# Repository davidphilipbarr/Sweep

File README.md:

# Sweep
<!--
           ___                        ___
      ___ |   | ___ ___      ___ ___ |   | ___
 ___ |   |`___`|   |   |    |   |   |`___`|   | ___
|   |`___`|   |`___`___`    `___`___`|   |`___`|   |
`___`|   |`___`|   |   |    |   |   |`___`|   |`___`
|   |`___`|   |`___`___`    `___`___`|   |`___`|   |
`___`|   |`___`|   |   |    |   |   |`___`|   |`___`
|   |`___`     `___`___`    `___`___`     `___`|   |
`___`           ___ ___      ___ ___           `___`
               |   |   |    |   |   |
               `___`___`    `___`___`
-->
>    
> <sub>Bluetooth Sweep 2 + MBK Legend Keycaps</sub>

<span>

</span>

## What is sweep?

Sweep is a version of the more fabulous [Ferris](https://github.com/pierrechevalier83/ferris) by [Pierre Chevalier](https://github.com/pierrechevalier83/) that uses a daughter board like a promicro, elite-c, bit-c, nice!nano etc. instead of using onboard components.

## What are the different types?

⭐ Sweep 2 - Recommended Choc v1 board with all the features.  
⭕ Sweep Half Swept - Same as Sweep 2, but with a reversible pro-micro footprint.  
⭕ Sweep Bling MX - An MX only Sweep that features Kailh's hotswap sockets and a stacked case.  
⭕ Sweep Bling LP - A Choc v1 only Sweep that features Kailh's hotswap sockets.  
⭕ Sweep High - Same as the Sweep 2, but trades choc spacing for compatibility with more switches and keycaps.  
⭕ Sweep High M - A soldered MX only Sweep, with a reversible PCB design.  
⭕ Sweep Mini - The only version that supports Choc minis.  
⭕ Sweep ULP - A version for the Cherry Ultra low profile switches.  

| Device | On/Off Switch<sup>[1]</sup> | Reversible PCB<sup>[2]</sup> | Choc V1 | Choc V2 | Choc Mini | MX & Alps | Cherry ULP | Choc Spacing<sup>[3]</sup> | Tenting<sup>[4]</sup> | Hot Swap |
| :--- | :---: | :---: | :---: | :---: | :---: | :---: | :---: | :---: | :---: | :---: |
| Sweep2.x          | ✔ |   | ✔ |   |   |   |   | ✔ | ✔ | Mill-Max (optional) |
| Sweep Bling LP    | ✔ |   | ✔ |   |   |   |   | ✔ | ✔ | Kailh (required) |
| Sweep Bling MX    | ✔ | ✔ |   |   |   | ⚠<br/><sup>[5]</sup> |   |   | ✔ | Kailh (required) |
| Sweep High        | ✔ |   | ✔ | ✔ |   | ✔ |   |   | ✔ |
| Sweep High M      | ✔ | ✔ |   |   |   | MX|   |   | ✔ |   |
| Sweep Half Swept  | ✔ | ✔ | ✔ |   |   |   |   | ✔ | ✔ | Mill-Max (optional) |
| Sweep Mini        |   | ✔ |   |   | ✔ |   |   | ✔ |   |
| Sweep ULP         | ✔ |   |   |   |   |   | ✔ | ✔ |   |

> Note: All versions support bluetooth with Nice!Nano

*<sup>[1]</sup> An on/off switch is recommended for bluetooth builds.*  
*<sup>[2]</sup> With a reversible PCB it's easier to make mistakes during assembly, but it allows you to purchase less boards.*  
*<sup>[3]</sup> Choc spaced boards have the switches in a tighter grid. This provides a better final look but is only compatible with some choc keycaps. (e.g. MBK)*  
*<sup>[4]</sup> Supports splitkb's [tenting puck.](https://splitkb.com/products/tenting-puck?_pos=1&_psq=tenting%20&_ss=e&_v=1.0)*  
*<sup>[5]</sup> MX + kailh hotswap ONLY. Alps are NOT supported.*  

## Components list

To build and use a Sweep you will need:

* 1x PCB Kit
* 2x promicro compatible boards or 2 nice!nanos.
* 34 switches of a compatible type (refer to the compatibility table)
* 34 keycaps
* 2x reset switches (optional; [B3U-1000P(M)](https://github.com/davidphilipbarr/Sweep/issues/20))
* Some little rubber feet/bumpers
* 2x power switches (optional if supported; MSK 12C02)
* 1x TRRS (not TRS!) cable (wired build only)
* 2x TRRS Jack [PJ-320A] (wired build only)
* 1 USB Cable (depends on your micro-controller choice)

## How do I make this thing?

## Firmware

The firmware can be found [with the Ferris  firmware as part of QMK](https://github.com/qmk/qmk_firmware/tree/master/keyboards/ferris/sweep).

Firmware for zmk and bluemicro_ble is called ["Cradio"](https://zmk.dev/docs/hardware/).

## Who made this?

* [Pierre Chevalier](https://github.com/pierrechevalier83)
* [David Barr](https://github.com/davidphilipbarr)
* [Ibnu Daru Aji](https://github.com/ibnuda/)
* [Duccio](https://github.com/duckyb)

## Featured Forks ✨

* [Sweep Gateron](https://github.com/drewlwhitney/Sweep-Gateron) by drewlwhitney: *A Sweep High modded with Gateron-LP KS-33 support.*

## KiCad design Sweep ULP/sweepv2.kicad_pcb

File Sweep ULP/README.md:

# Sweep2

This is the ultra low profile version of the sweep.

## Ordering The PCB

To order the PCB the following settings are recommended<sup>1,2</sup>:

|Detail|Value|
|---|---|
|Gerber file|`production/sweepv2.zip`|
|Base material|FR-4|
|Layers|2|
|Dimension|216.9mm x 86.9mm|
|Different design|2|
|Delivery format|Panel by customer|
|PCB thickness|0.6mm|
|PCB color|(Personal preference)|
|Silkscreen|(Personal preference)|
|Surface finish|(Personal preference)|
|Outer copper weight|1oz|
|Gold Fingers|No|
|Confirm production file|No|
|Castellated holes|No|
|Remove order number|Yes|

1: Settings are for [JLCPCB](https://jlcpcb.com/), but could work for other manufacturers.

2: Settings are taken from [Kyek's video guide](https://www.youtube.com/watch?v=fBPu7AyDtkM&t=17s).

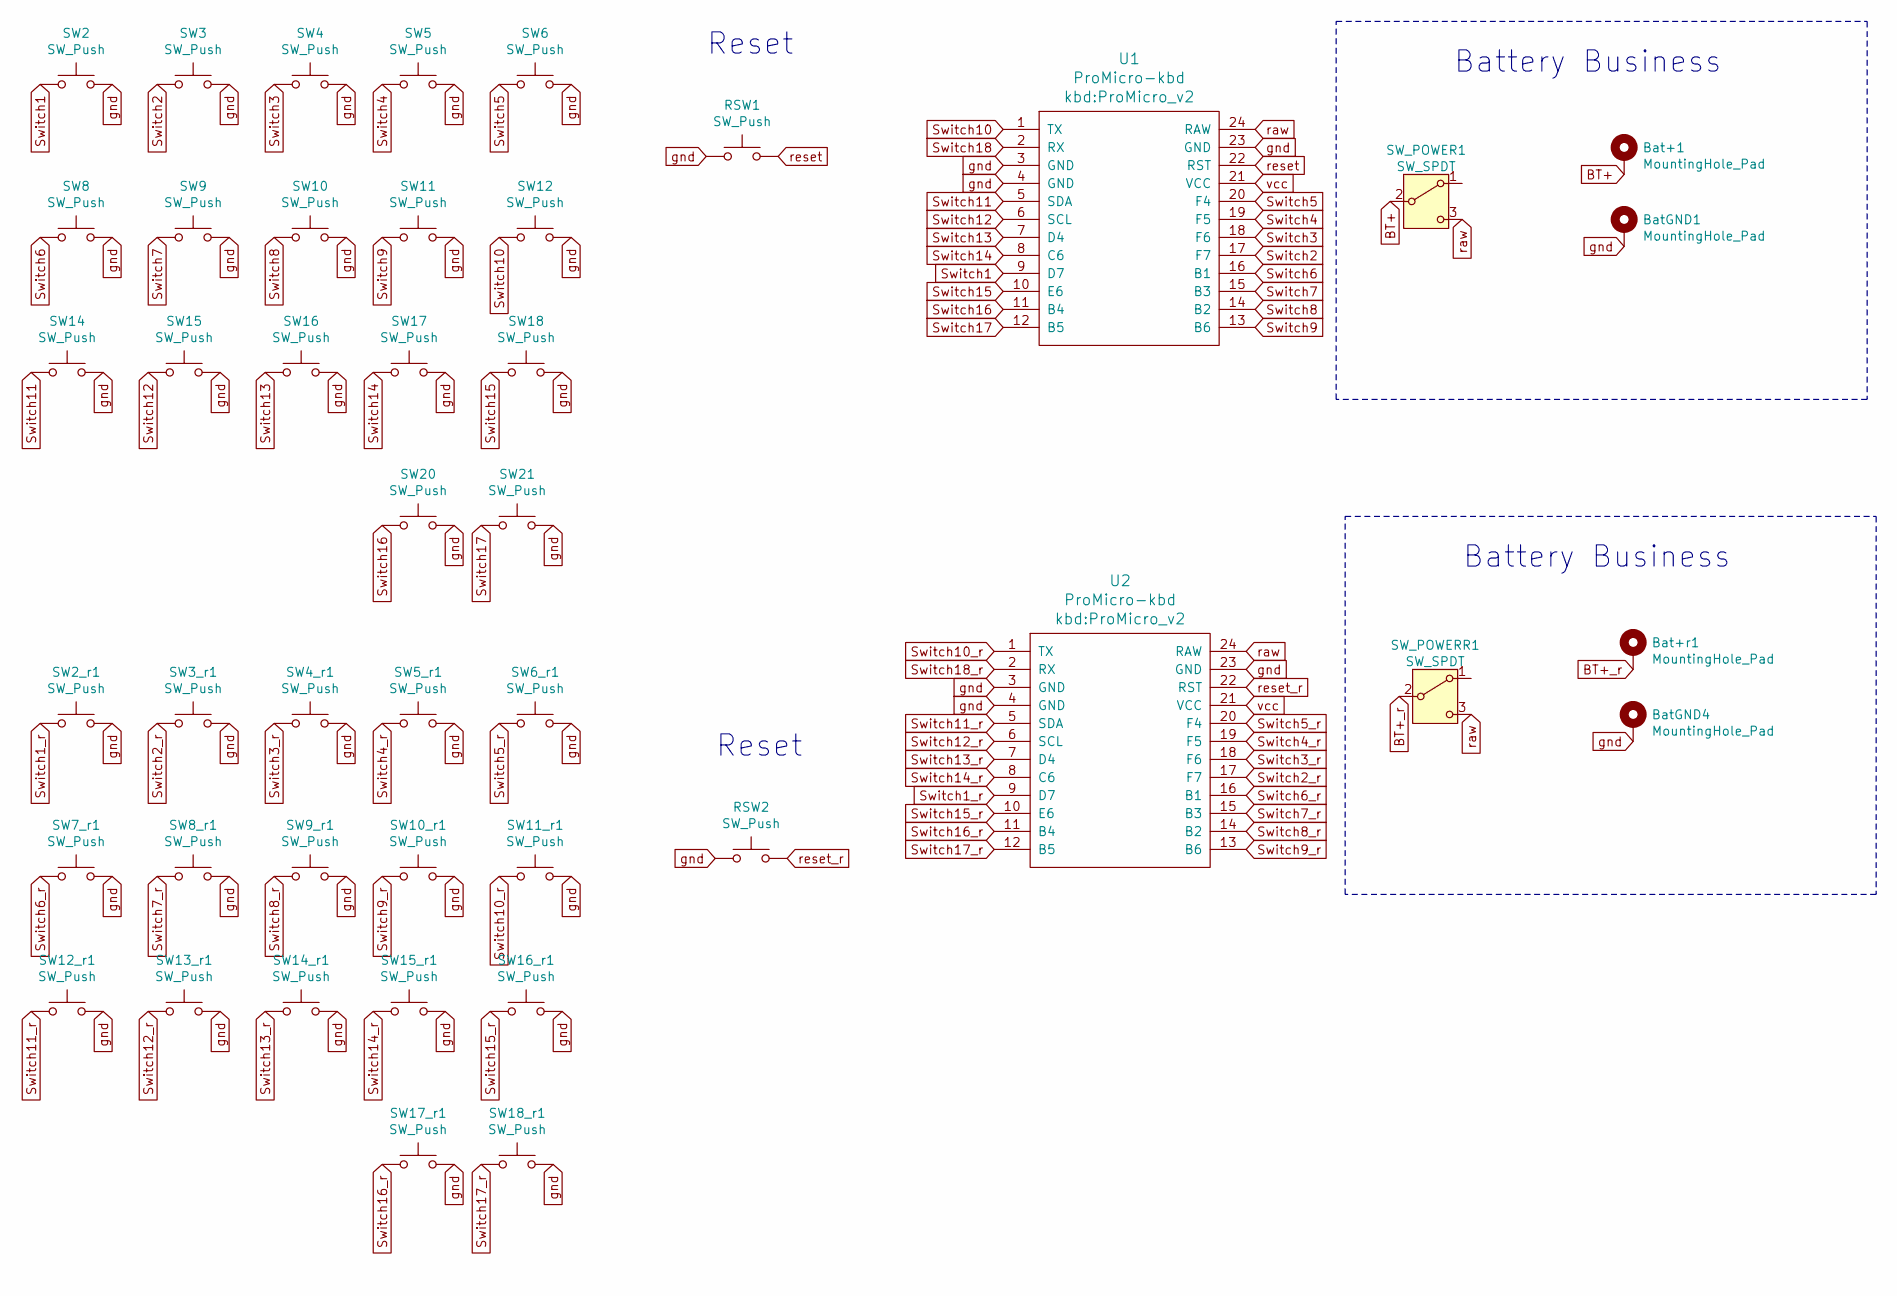
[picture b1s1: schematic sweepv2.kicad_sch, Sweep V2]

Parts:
Bat+1: MountingHole_Pad; 1pin_conn
Bat+r1: MountingHole_Pad; 1pin_conn
BatGND1, BatGND4: MountingHole_Pad; 1pin_conn
RSW1, RSW2: SW_Push; ResetSW
SW2, SW2_r1, SW3, SW3_r1, SW4, SW4_r1, SW5, SW5_r1, SW6, SW6_r1, SW7_r1, SW8, SW8_r1, SW9, SW9_r1, SW10, SW10_r1, SW11, SW11_r1, SW12, SW12_r1, SW13_r1, SW14, SW14_r1, SW15, SW15_r1, SW16, SW16_r1, SW17, SW17_r1, SW18, SW18_r1, SW20, SW21: SW_Push; Cherry_ULP_TH_CUT_3D
SW_POWER1: SW_SPDT; SPDT_C128955
SW_POWERR1: SW_SPDT; SPDT_C128955
U1, U2: ProMicro-kbd; ProMicro_v2

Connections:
BT+: Bat+1.1, SW_POWER1.2 (B)
BT+_r: Bat+r1.1, SW_POWERR1.2 (B)
Switch1: SW2.1, U1.9 (D7)
Switch1_r: SW2_r1.1, U2.9 (D7)
Switch2: SW3.1, U1.17 (F7)
Switch2_r: SW3_r1.1, U2.17 (F7)
Switch3: SW4.1, U1.18 (F6)
Switch3_r: SW4_r1.1, U2.18 (F6)
Switch4: SW5.1, U1.19 (F5)
Switch4_r: SW5_r1.1, U2.19 (F5)
Switch5: SW6.1, U1.20 (F4)
Switch5_r: SW6_r1.1, U2.20 (F4)
Switch6: SW8.1, U1.16 (B1)
Switch6_r: SW7_r1.1, U2.16 (B1)
Switch7: SW9.1, U1.15 (B3)
Switch7_r: SW8_r1.1, U2.15 (B3)
Switch8: SW10.1, U1.14 (B2)
Switch8_r: SW9_r1.1, U2.14 (B2)
Switch9: SW11.1, U1.13 (B6)
Switch9_r: SW10_r1.1, U2.13 (B6)
Switch10: SW12.1, U1.1 (TX)
Switch10_r: SW11_r1.1, U2.1 (TX)
Switch11: SW14.1, U1.5 (SDA)
Switch11_r: SW12_r1.1, U2.5 (SDA)
Switch12: SW15.1, U1.6 (SCL)
Switch12_r: SW13_r1.1, U2.6 (SCL)
Switch13: SW16.1, U1.7 (D4)
Switch13_r: SW14_r1.1, U2.7 (D4)
Switch14: SW17.1, U1.8 (C6)
Switch14_r: SW15_r1.1, U2.8 (C6)
Switch15: SW18.1, U1.10 (E6)
Switch15_r: SW16_r1.1, U2.10 (E6)
Switch16: SW20.1, U1.11 (B4)
Switch16_r: SW17_r1.1, U2.11 (B4)
Switch17: SW21.1, U1.12 (B5)
Switch17_r: SW18_r1.1, U2.12 (B5)
Switch18: U1.2 (RX)
Switch18_r: U2.2 (RX)
gnd: BatGND1.1, BatGND4.1, RSW1.1, RSW2.1, SW2.2, SW2_r1.2, SW3.2, SW3_r1.2, SW4.2, SW4_r1.2, SW5.2, SW5_r1.2, SW6.2, SW6_r1.2, SW7_r1.2, SW8.2, SW8_r1.2, SW9.2, SW9_r1.2, SW10.2, SW10_r1.2, SW11.2, SW11_r1.2, SW12.2, SW12_r1.2, SW13_r1.2, SW14.2, SW14_r1.2, SW15.2, SW15_r1.2, SW16.2, SW16_r1.2, SW17.2, SW17_r1.2, SW18.2, SW18_r1.2, SW20.2, SW21.2, U1.3 (GND), U1.4 (GND), U1.23 (GND), U2.3 (GND), U2.4 (GND), U2.23 (GND)
raw: SW_POWER1.3 (C), SW_POWERR1.3 (C), U1.24 (RAW), U2.24 (RAW)
reset: RSW1.2, U1.22 (RST)
reset_r: RSW2.2, U2.22 (RST)
vcc: U1.21 (VCC), U2.21 (VCC)

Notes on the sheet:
Battery Business
Reset

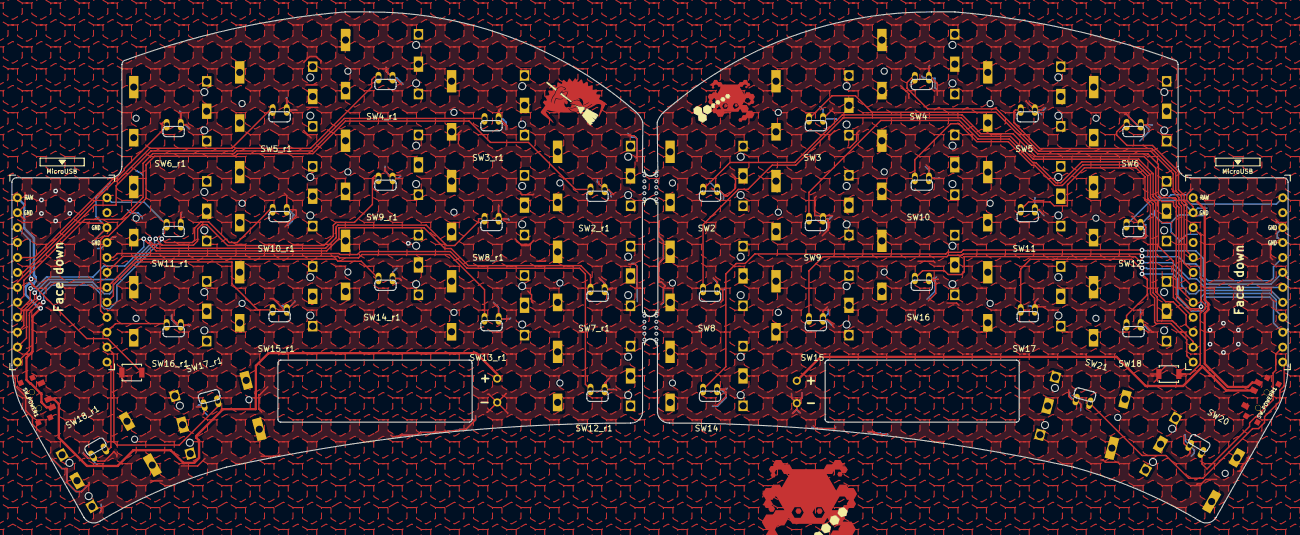
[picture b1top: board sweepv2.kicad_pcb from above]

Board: 2 copper layers, 216.9 x 86.9 mm, 46 parts (0 on the bottom side), 41 nets.

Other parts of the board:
mouse-bite-2mm-slot, mouse-bite-2mm-slot#2: VAL**; mouse-bite-5mm-slot-with-space-for-track

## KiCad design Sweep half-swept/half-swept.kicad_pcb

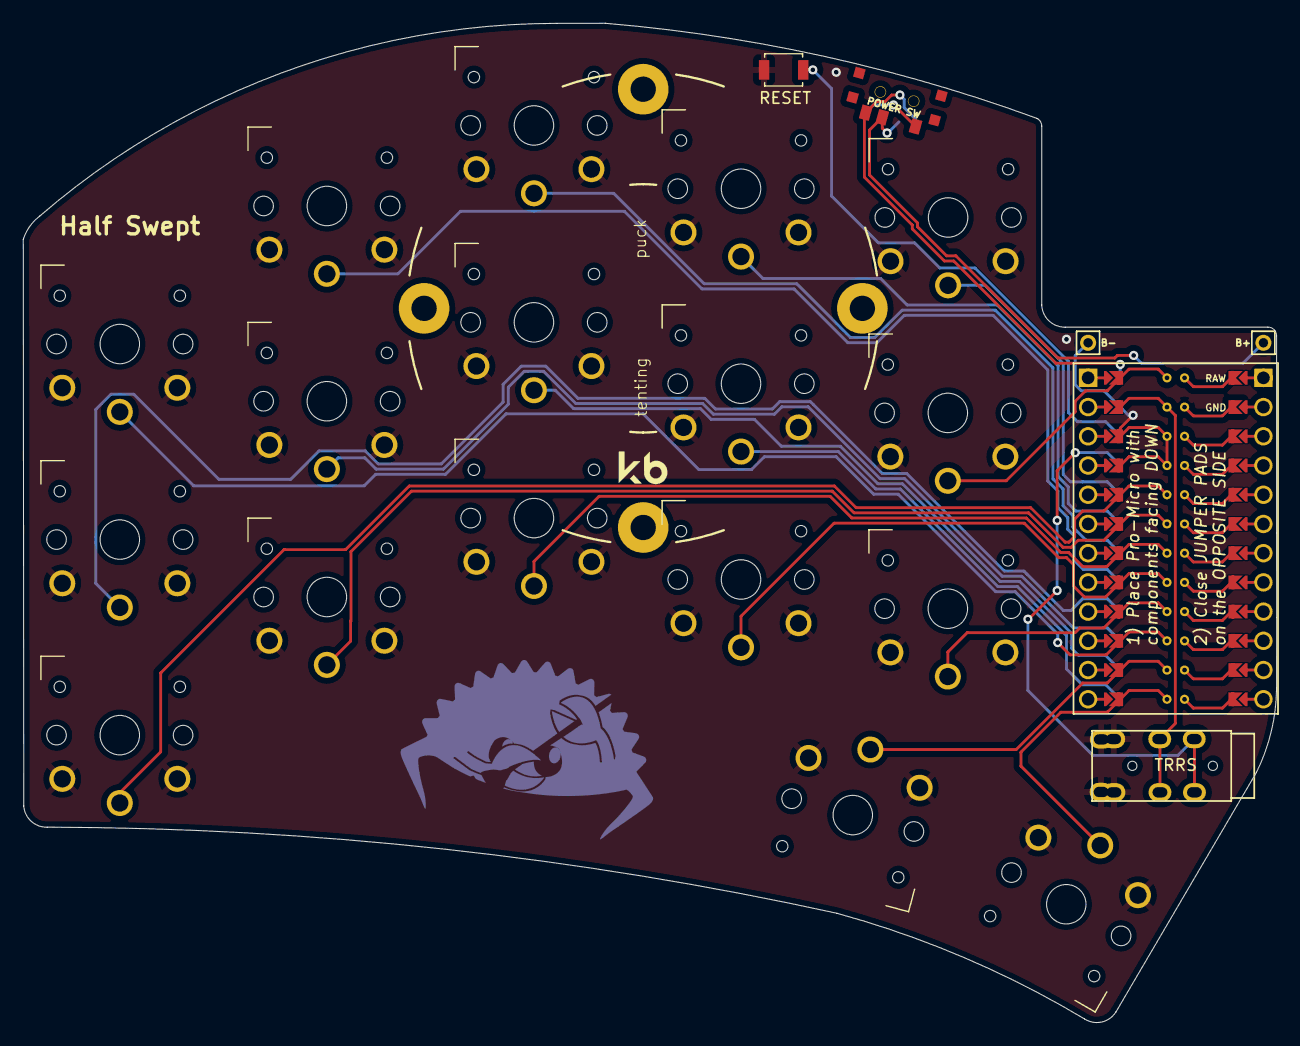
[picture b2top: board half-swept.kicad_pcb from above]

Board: 2 copper layers, 109.0 x 86.9 mm, 23 parts (0 on the bottom side), 23 nets.

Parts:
B+: MountingHole_Pad; 1pin_conn
B-: MountingHole_Pad; 1pin_conn
J2: AudioJack4dpb; TRRS-PJ-DPB2
POWER SW: SW_SPDT; SPDT_C128955
RSW2: SW_Push; Tactile-Switch_SMT
SW1, SW2, SW3, SW4, SW5, SW6, SW7, SW8, SW9, SW10, SW11, SW12, SW13, SW14, SW15, SW16, SW17: SW_Push; SW_PG1350_rev_DPB
U1: ProMicro-kbd; ProMicro_jumpers_facedown

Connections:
BT+_r: B+.1, POWER SW.2
Switch1: SW1.1, U1.10
Switch2: SW2.1, U1.17
Switch3: SW3.1, U1.18
Switch4: SW4.1, U1.19
Switch5: SW5.1, U1.20
Switch6: SW6.1, U1.16
Switch7: SW7.1, U1.15
Switch8: SW8.1, U1.14
Switch9: SW9.1, U1.13
Switch10: SW10.1, U1.1
Switch11: SW11.1, U1.5
Switch12: SW12.1, U1.6
Switch13: SW13.1, U1.7
Switch14: SW14.1, U1.8
Switch15: SW15.1, U1.9
Switch16: SW16.1, U1.11
Switch17: SW17.1, U1.12
Switch18: J2.R1, U1.2
gnd: B-.1, J2.S, J2.T, RSW2.1, RSW2.2, SW1.2, SW2.2, SW3.2, SW4.2, SW5.2, SW6.2, SW7.2, SW8.2, SW9.2, SW10.2, SW11.2, SW12.2, SW13.2, SW14.2, SW15.2, SW16.2, SW17.2, U1.3, U1.4, U1.23
raw: POWER SW.3, U1.24
reset: RSW2.1, RSW2.2, U1.22
vcc: J2.R2, U1.21

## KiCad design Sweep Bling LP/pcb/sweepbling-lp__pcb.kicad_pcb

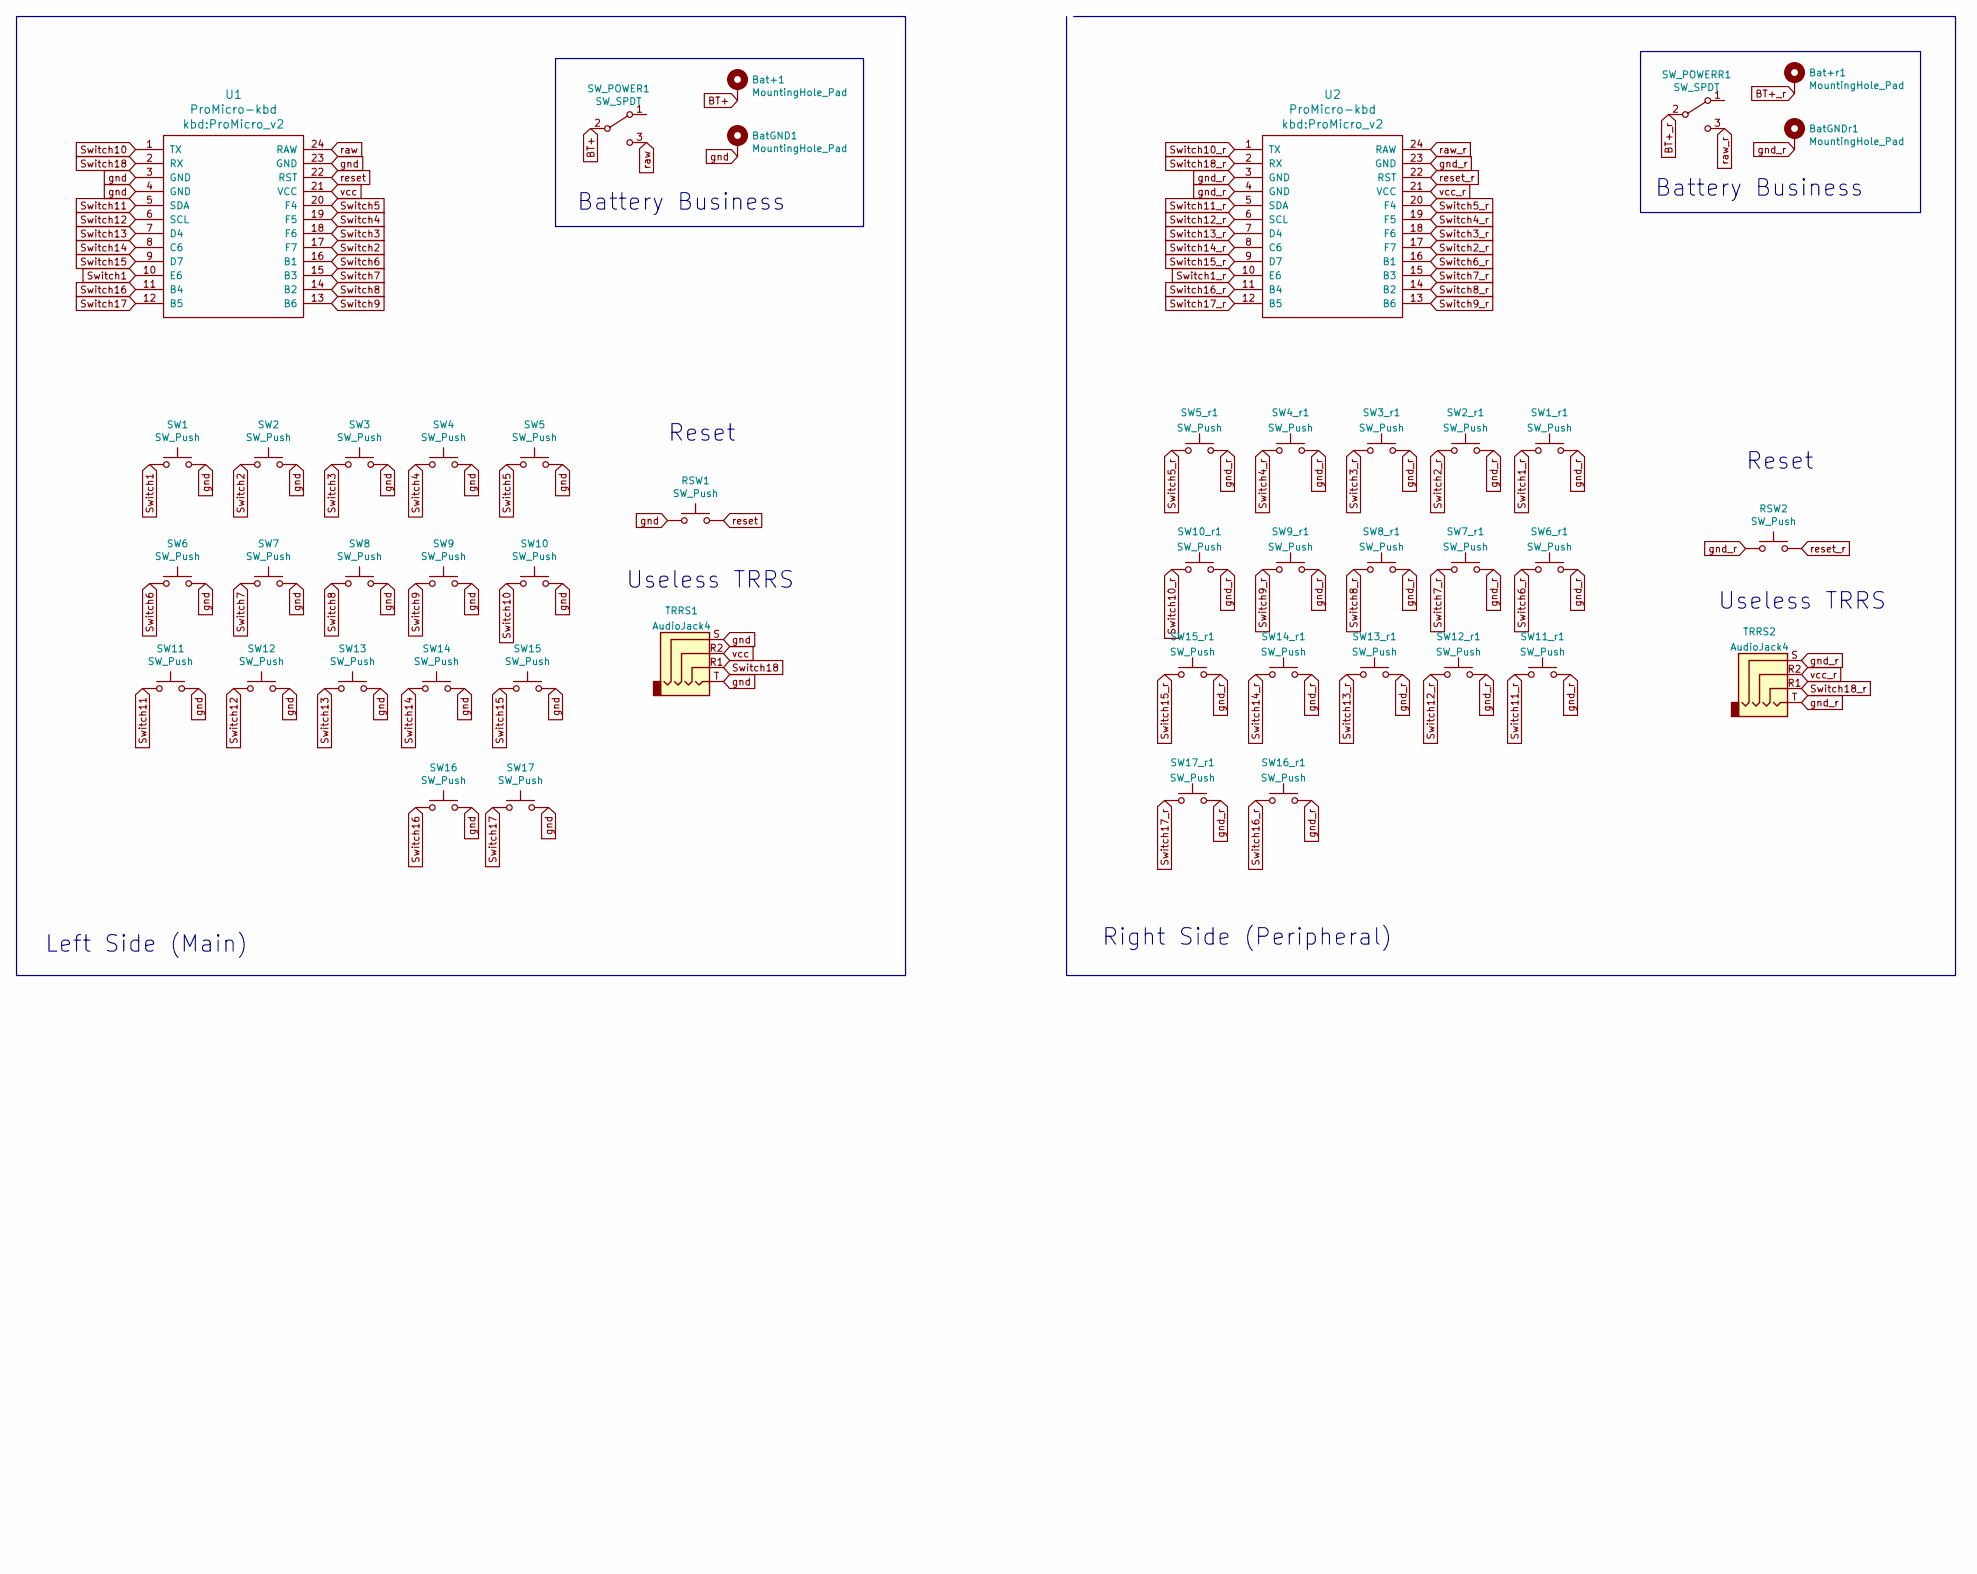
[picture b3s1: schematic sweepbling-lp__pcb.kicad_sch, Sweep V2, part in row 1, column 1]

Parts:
Bat+1: MountingHole_Pad; 1pin_conn
Bat+r1: MountingHole_Pad; 1pin_conn
BatGND1: MountingHole_Pad; 1pin_conn
BatGNDr1: MountingHole_Pad; 1pin_conn
RSW1, RSW2: SW_Push; ResetSW
SW1, SW1_r1, SW2, SW2_r1, SW3, SW3_r1, SW4, SW4_r1, SW5, SW5_r1, SW6, SW6_r1, SW7, SW7_r1, SW8, SW8_r1, SW9, SW9_r1, SW10, SW10_r1, SW11, SW11_r1, SW12, SW12_r1, SW13, SW13_r1, SW14, SW14_r1, SW15, SW15_r1, SW16, SW16_r1, SW17, SW17_r1: SW_Push; SW_PG1350_rev_DPB
SW_POWER1: SW_SPDT; SPDT_C128955
SW_POWERR1: SW_SPDT; SPDT_C128955
TRRS1, TRRS2: AudioJack4
U1, U2: ProMicro-kbd; ProMicro_v2

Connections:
BT+: Bat+1.1, SW_POWER1.2 (B)
BT+_r: Bat+r1.1, SW_POWERR1.2 (B)
Switch1: SW1.1, U1.10 (E6)
Switch1_r: SW1_r1.1, U2.10 (E6)
Switch2: SW2.1, U1.17 (F7)
Switch2_r: SW2_r1.1, U2.17 (F7)
Switch3: SW3.1, U1.18 (F6)
Switch3_r: SW3_r1.1, U2.18 (F6)
Switch4: SW4.1, U1.19 (F5)
Switch4_r: SW4_r1.1, U2.19 (F5)
Switch5: SW5.1, U1.20 (F4)
Switch5_r: SW5_r1.1, U2.20 (F4)
Switch6: SW6.1, U1.16 (B1)
Switch6_r: SW6_r1.1, U2.16 (B1)
Switch7: SW7.1, U1.15 (B3)
Switch7_r: SW7_r1.1, U2.15 (B3)
Switch8: SW8.1, U1.14 (B2)
Switch8_r: SW8_r1.1, U2.14 (B2)
Switch9: SW9.1, U1.13 (B6)
Switch9_r: SW9_r1.1, U2.13 (B6)
Switch10: SW10.1, U1.1 (TX)
Switch10_r: SW10_r1.1, U2.1 (TX)
Switch11: SW11.1, U1.5 (SDA)
Switch11_r: SW11_r1.1, U2.5 (SDA)
Switch12: SW12.1, U1.6 (SCL)
Switch12_r: SW12_r1.1, U2.6 (SCL)
Switch13: SW13.1, U1.7 (D4)
Switch13_r: SW13_r1.1, U2.7 (D4)
Switch14: SW14.1, U1.8 (C6)
Switch14_r: SW14_r1.1, U2.8 (C6)
Switch15: SW15.1, U1.9 (D7)
Switch15_r: SW15_r1.1, U2.9 (D7)
Switch16: SW16.1, U1.11 (B4)
Switch16_r: SW16_r1.1, U2.11 (B4)
Switch17: SW17.1, U1.12 (B5)
Switch17_r: SW17_r1.1, U2.12 (B5)
Switch18: TRRS1.R1, U1.2 (RX)
Switch18_r: TRRS2.R1, U2.2 (RX)
gnd: BatGND1.1, RSW1.1, SW1.2, SW2.2, SW3.2, SW4.2, SW5.2, SW6.2, SW7.2, SW8.2, SW9.2, SW10.2, SW11.2, SW12.2, SW13.2, SW14.2, SW15.2, SW16.2, SW17.2, TRRS1.S, TRRS1.T, U1.3 (GND), U1.4 (GND), U1.23 (GND)
gnd_r: BatGNDr1.1, RSW2.1, SW1_r1.2, SW2_r1.2, SW3_r1.2, SW4_r1.2, SW5_r1.2, SW6_r1.2, SW7_r1.2, SW8_r1.2, SW9_r1.2, SW10_r1.2, SW11_r1.2, SW12_r1.2, SW13_r1.2, SW14_r1.2, SW15_r1.2, SW16_r1.2, SW17_r1.2, TRRS2.S, TRRS2.T, U2.3 (GND), U2.4 (GND), U2.23 (GND)
raw: SW_POWER1.3 (C), U1.24 (RAW)
raw_r: SW_POWERR1.3 (C), U2.24 (RAW)
reset: RSW1.2, U1.22 (RST)
reset_r: RSW2.2, U2.22 (RST)
vcc: TRRS1.R2, U1.21 (VCC)
vcc_r: TRRS2.R2, U2.21 (VCC)

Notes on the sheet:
Battery Business
Useless TRRS
Reset
Left Side (Main)
Right Side (Peripheral)

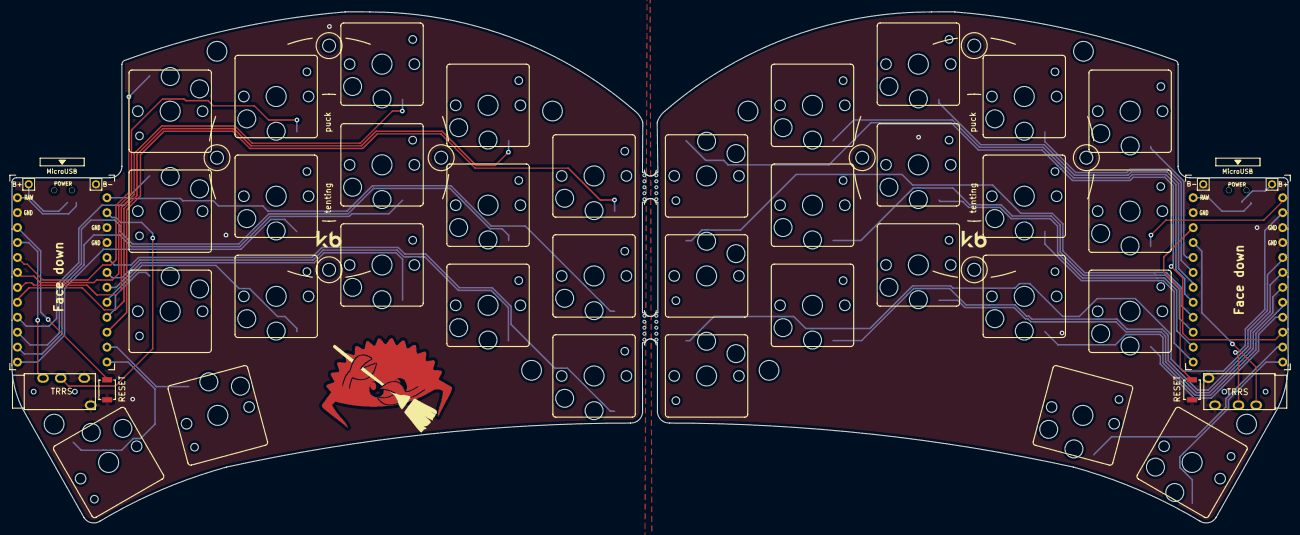
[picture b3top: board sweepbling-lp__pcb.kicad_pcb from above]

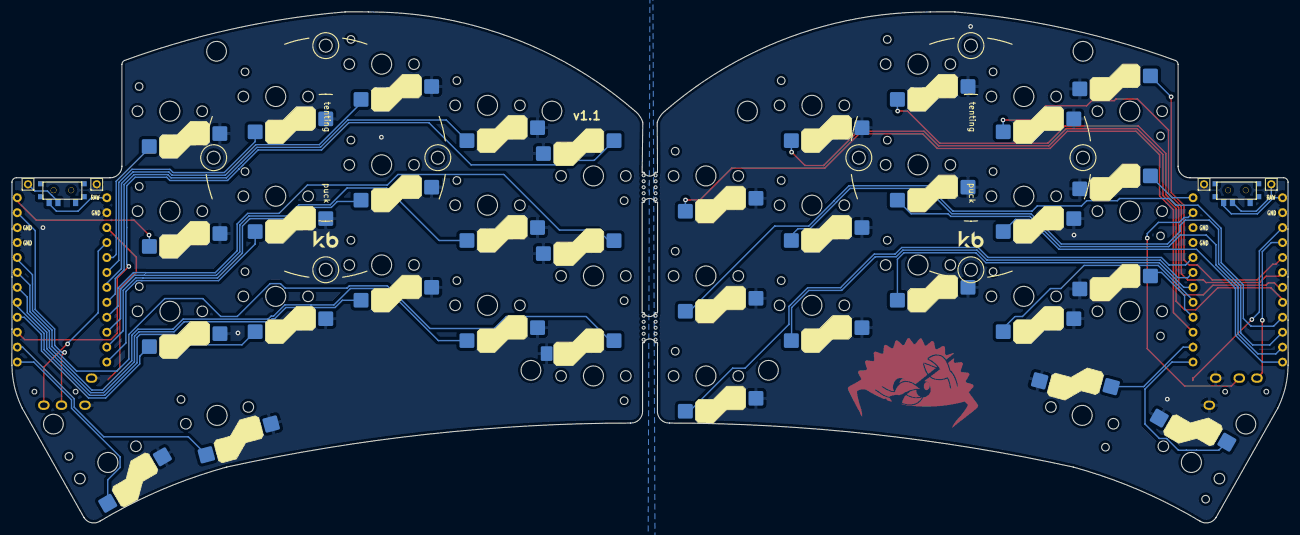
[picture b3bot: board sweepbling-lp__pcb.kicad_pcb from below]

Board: 2 copper layers, 216.9 x 86.9 mm, 51 parts (2 on the bottom side), 46 nets.

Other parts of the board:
REF_PUCK_R: Tenting Puck; Tenting_Puck2_no_pads
SweepLogo: LOGO; ferris_broom
e: Tenting Puck; Tenting_Puck2_no_pads
mouse-bite-2mm-slot1, mouse-bite-2mm-slot2: VAL**; mouse-bite-5mm-slot-with-space-for-track

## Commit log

2020-11-24 Hello new sweep home
2020-11-24 speeeeling
2020-12-06 add ble
2020-12-09 update gerber
2021-01-22 update stagger and routing
2021-01-22 update stagger
2021-02-06 Clarify promicro orientation during building
    I unfortunately made this mistake during building, as have one or two people on the 40% Keyboards Discord.
2021-02-08 Add controller directional hint to pcb as well.
2021-05-07 Add version 2 of sweep, untested, may be dragons.
2021-05-07 add snaps
2021-05-07 bom comment changes
2021-05-07 better switch placement but still actually all over, don't use.
2021-05-08 better alignment?
2021-05-26 fix thumb keys
2021-07-26 pcbs are flip-able for optional up-facing controllers, add top plate
    allow the pcbs to be flipped so you can use a bugger battery under nice!nano (potentially) add top plate.
    Untested...
2021-07-26 update a bit for sweep 2
2021-07-27 resets and trrs
2021-07-28 remove all the reversible bits
    back to one sided.
2021-08-03 flippable version of sweep2
    Useful for allpcb, some larger battery use cases, etc. generally a waste of time, use sweep2.
2021-09-10 address issues raised...
    'fix' the silk issue. change the way the boards are joined, move the controllers slightly away from edge, slight re route. add a bit of text about the ferris?
2021-09-10 remove pointless trace
2021-09-13 First upload of mx/choc2/alps version.
    Here there be dragons.
2021-09-21 fix vcc tidy up routing
2021-10-17 Add license from ferris...
2021-10-27 add power switch part number, thanks Cem Aksoylar!
2021-10-27 add YouTube video by kyek
2021-11-04 Add comparison chart
    Reduce user confusion in picking the correct device with a comparison chart. Description texts are also updated and the Sweep HIGH is added.
2021-11-04 Remove reversible PCB from Sweep High
2021-11-04 Update sweep high row, add "choc spacing" column
2021-11-11 Add sweep half swept to the table
2021-11-11 Recommend half swept over compact
2021-11-15 add gerber from Karl, that should work.
2021-11-15 add tentative 2.1
2021-11-19 superflous routing.
2021-11-19 should fix #16
2021-11-19 Refactor repository and fix breakaway tabs
2021-11-20 Add gerbers
2021-11-20 Update readmes
2021-11-20 Add links to qmk and zmk
2021-11-20 Add splash image
2021-11-22 replace reversible switch footprint
2021-11-26 doc(sweepv2.1): Added PCB ordering values to README
2021-11-27 fix(pr-feedback): Updated phrasing
2021-11-27 fix(pr-feedback): Added PCB ordering to Sweep 2 and HIGH READMEs
2021-11-29 Update gerbers and add gitignore
2021-11-30 fix(pr-feedback): Use correct dimensions for sweep high
2021-12-06 simplified sweep high for all pcb usage
    Half a sweep high.
2021-12-21 Update silk and edge cuts
2021-12-21 Remove B5 label and update gerber
2021-12-21 Add optional top plate files
2021-12-24 Re-arrange readme
2022-01-01 Ignore and remove fp-info-cache
2022-01-16 Create sweep bling mx
2022-01-17 Update silk and MCU orientation
2022-01-17 Run auto router
2022-01-17 Flip MCU pads for face down and re-route
2022-01-18 Add partial manual routing
2022-01-18 Finish manual routing
2022-01-18 Fix DRC issues
2022-01-18 Update readmes and gerbers
2022-01-18 Add kailh sockets to readme
2022-01-18 Add sweep bling mx renders
2022-01-29 add plate pcb files
2022-02-01 Added Keyboard Layout Editor Information
2022-02-13 Add switch plate xdf
2022-02-13 Update version number on PCB (v1.0)
2022-02-13 Remove pre-release warnings
2022-02-15 Archive sweep 2.0
2022-03-16 Fix delivery format
2022-03-29 Remove alignment target from Bling MX
2022-04-17 PCB modifications
    -Relocated TRRS port
    -New PCB cutout
    -Removed reset button
2022-04-21 removed excess projects
2022-04-24 Enlarge slots to .5mm
2022-04-24 Fix silk screen
2022-04-24 Fix DRC issues on edge
2022-04-25 Fix tracks and update gerber
2022-04-28 Create philosophy
2022-04-28 add links
2022-05-01 Add support for millmax sockets
2022-05-01 Rename backups folder
2022-05-01 Update version in README
2022-05-01 Update gerber version in README
2022-05-09 Fix PCB measurements
2022-05-10 Fix for issue#39
2022-05-10 Remove accidentally added bling lp plate
2022-05-15 Add Sweep Bling LP PCB
2022-05-15 Fix schematic
2022-05-15 Add gerber
2022-05-15 Update version table
2022-05-17 Add workflow
2022-05-17 Update board preview
2022-05-17 Fix bling mx malformed outline
2022-05-17 Fix DRC on sweep high m
2022-05-17 Update bottom plate malformed edge cuts
2022-05-17 Update all READMEs, Add pcbdraw output
2022-05-18 Update pcbdraw theme
2022-05-18 Use blue pcb for previews
2022-05-18 Update bling mx fill zones
2022-05-18 Revert "Update bling mx fill zones"
    This reverts commit 3a15cb16145cf41150a782c0904b577e07dc4e4a.
2022-05-18 Update sweep half swept
2022-05-18 Add RAW/GND label, update gerber.zip
2022-05-19 Update compact low
2022-05-25 Update bling-lp pcb
2022-05-25 Update gallery (automated)
2022-05-25 Fix typo
2022-08-08 Update table
2022-09-02 Update Sweep naming system
2022-09-02 Update table and descriptions
2022-09-25 Add PDF of the schematic
2022-11-11 Added ascii art for terminal readers
2022-11-17 Fix Bling-MX plate file & gerber
2023-02-01 Update Bling LP spacer hole diameter & gerber
2023-02-01 Update Bling MX spacer hole diameter, silk & gerber
2023-08-29 Add hero image
2023-08-30 Improve centering on hero image and remove brand logo
2023-10-24 Fix typo in sweep high readme
2023-11-05 Panel by customer -> Single PCB
2024-01-20 Move misplace silkscreen labels for SW16 and SW17. FIX #83
2024-01-23 Fixes #81 adds plate
